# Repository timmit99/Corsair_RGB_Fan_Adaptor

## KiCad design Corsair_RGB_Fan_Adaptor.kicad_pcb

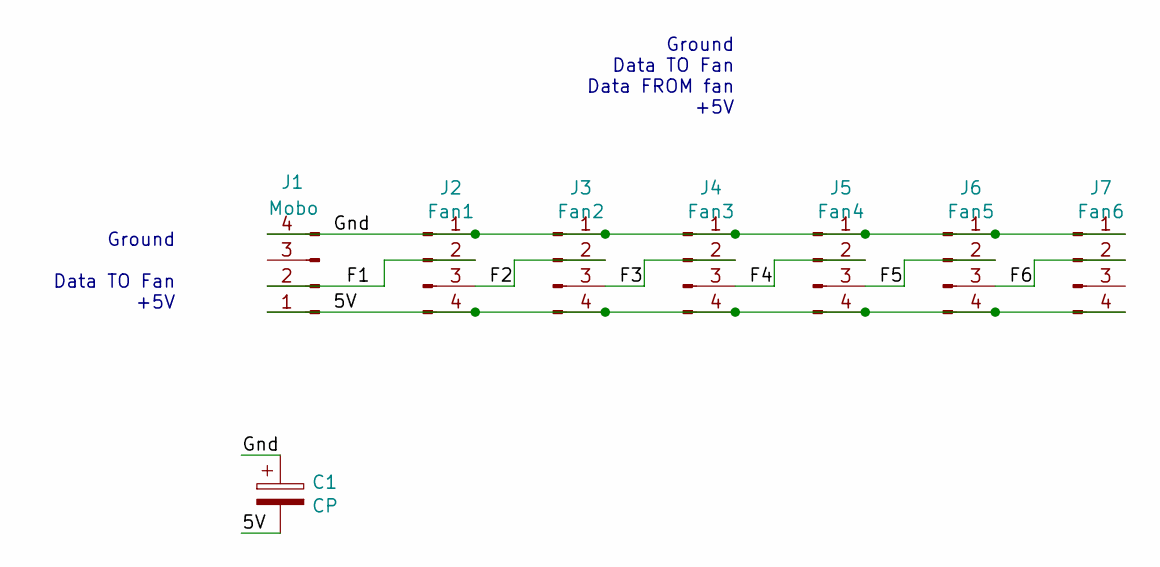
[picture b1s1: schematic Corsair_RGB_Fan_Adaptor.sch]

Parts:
C1: CP; CP_Radial_D6.3mm_P2.50mm
J1: Mobo; PinHeader_1x04_P2.54mm_Horizontal
J2: Fan1; 70553-000
J3: Fan2; 70553-000
J4: Fan3; 70553-000
J5: Fan4; 70553-000
J6: Fan5; 70553-000
J7: Fan6; 70553-000

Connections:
/5V: C1.2, J1.1, J2.4, J3.4, J4.4, J5.4, J6.4, J7.4
/F1: J1.2, J2.2
/F2: J2.3, J3.2
/F3: J3.3, J4.2
/F4: J4.3, J5.2
/F5: J5.3, J6.2
/F6: J6.3, J7.2
/Gnd: C1.1, J1.4, J2.1, J3.1, J4.1, J5.1, J6.1, J7.1

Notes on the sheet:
Ground Data TO Fan Data FROM fan +5V
Ground Data TO Fan +5V

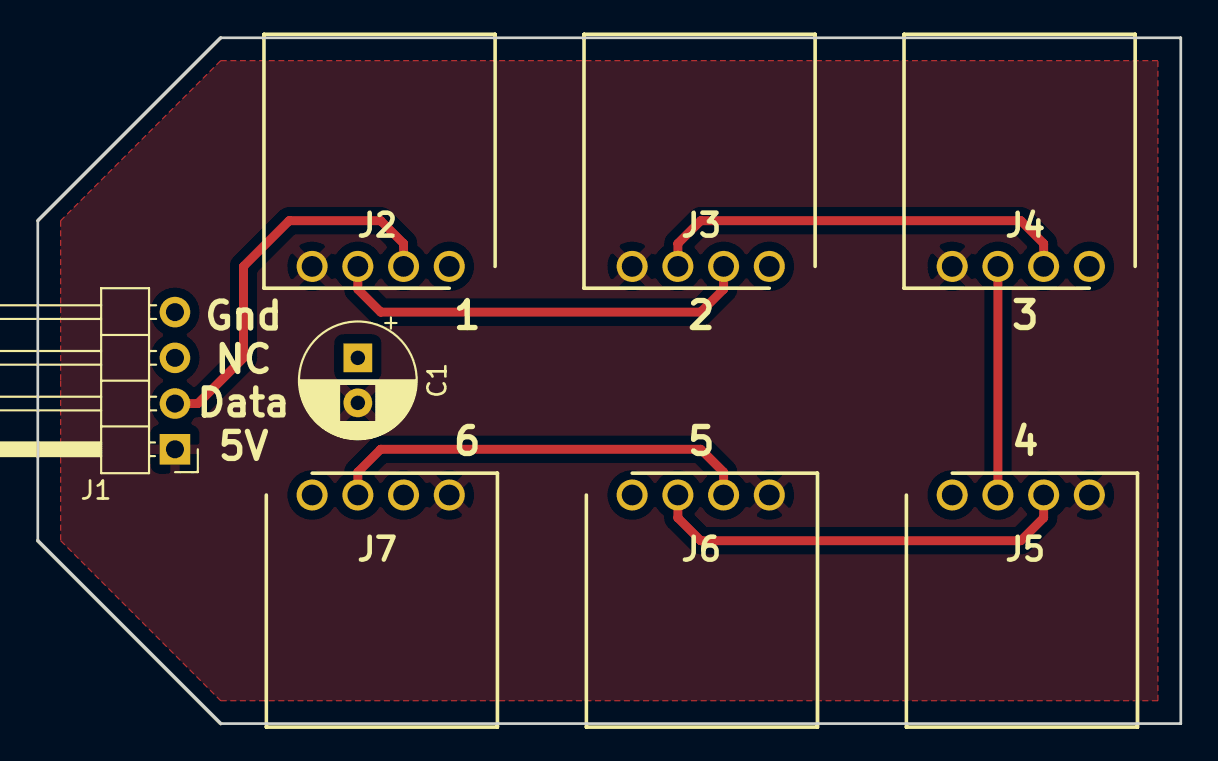
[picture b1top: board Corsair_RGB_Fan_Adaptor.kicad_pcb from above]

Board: 2 copper layers, 63.5 x 38.1 mm, 8 parts (0 on the bottom side), 8 nets.

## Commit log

2019-04-23 initial comit
2019-04-27 Filter Capacitor
    Adding filter capacitor to board for smoothing 5V power input.
2019-04-27 fix Project file
    Accidently added a "." to the .pro file.
2019-10-08 added some labeling to the PCB
    Added labels for numbering and locations
